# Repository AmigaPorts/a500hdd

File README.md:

# Amiga 500 ATA hard disk interface

Floppy-bootable HDD interface for Amiga 500. Achieves 600kB/s speed on
unexpanded system. Works well with kickstart 1.3 and 2.0.

Should you have two HDD expansions mounted for same address space, you can
invert master/slave select with a set of jumpers so that both can theoretically
coexist.

This board is bundled with side expansion adapter, which converts hard-to-get
edge connector into common pin header. For user convenience and safety of
PC mainboards with ISA slots, future expansions will be developed with pin
headers as their main connector.

**NOTE:** it is strongly recommended to wait for another revision of the board
since Rev2 has some minor, but annoying bugs.

## Release structure

Binary and gerber files are only packaged in releases.
For gerbers see `board/gerber` directory.
For device/software binaries see `software/bin` and `device/bin` directories.

## Documentation

If you feel that anything here needs elaborating, feel free to submit an issue.

- [Assembly](doc/assembly.md)
- [Preparing boot floppy](doc/floppy.md)
- [Formatting HDD for Amiga use](doc/formatting.md)

## License

Project's PCB designed is licensed under Creative Commons Attribution
Share-Alike (CC BY-SA) and is based on
[a500hdd](http://nuclear.mutantstargoat.com/hw/amiga/a500hdd)
by [John Tsiombikas](mailto:nuclear@member.fsf.org).

Code is licensed under Mozilla Public License version 2 (MPL2).
Original sources are taken from TODO project by TODO and TODO.

TL;DR: You have to publish your changes under same license, marking PCB design
with notice similar to one found in this project. For code changes, each file
with MPL header you modify must be published under same license.
Sharing is caring.

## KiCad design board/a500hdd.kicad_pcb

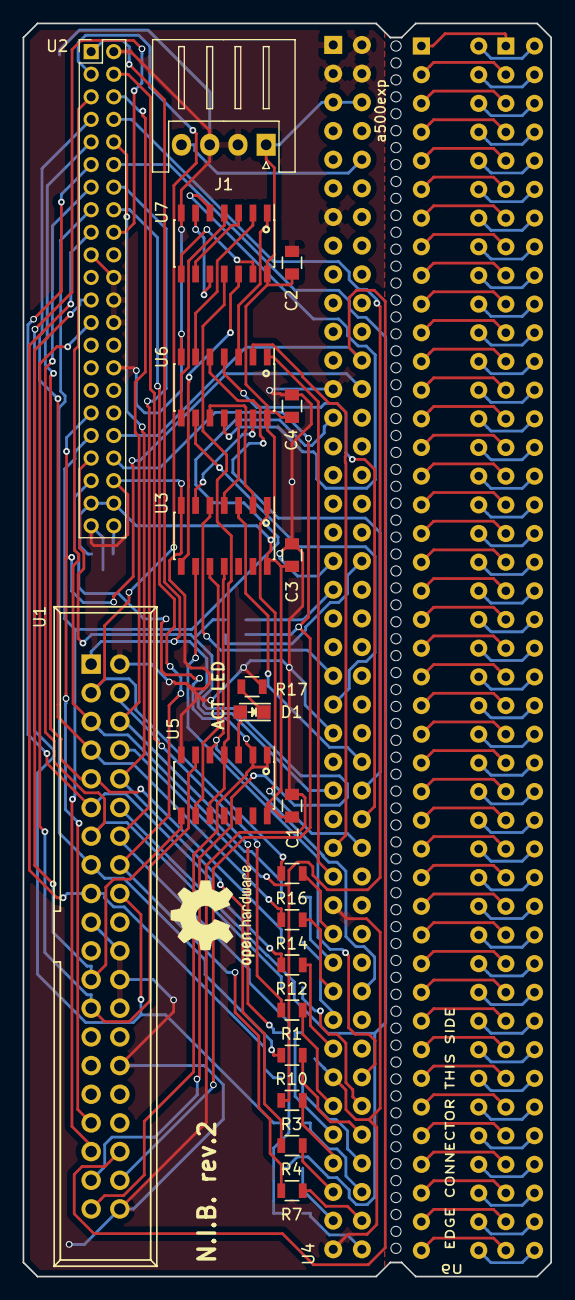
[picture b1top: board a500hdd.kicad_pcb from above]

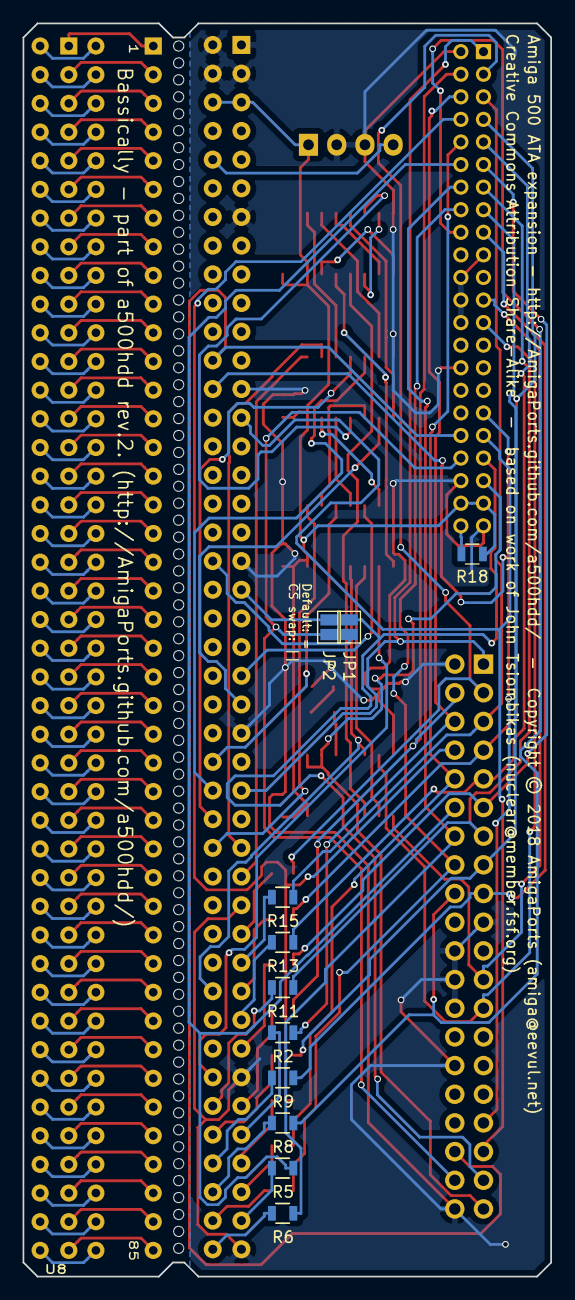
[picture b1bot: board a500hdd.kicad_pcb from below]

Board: 2 copper layers, 46.8 x 111.0 mm, 35 parts (11 on the bottom side), 158 nets.

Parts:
C1, C2, C3, C4: 0.1uF; C_0805
D1: LED; LED_0805
J1: Conn_01x04_Male; JST_XH_S04B-XH-A_1x04_P2.50mm_Horizontal
JP1, JP2: SolderJumper_2_Bridged; SolderJumper-2_P1.3mm_Open_Pad1.0x1.5mm
R1, R2, R3, R4, R5, R6, R7, R8, R9, R10, R11, R12, R13, R14, R15, R16: 68R; R_0805
R17: 330R; R_0805
R18: 4k7; R_0805
U1: ata_connector; IDC_Header_Straight_40pins
U2: ata_connector44; Pin_Header_Straight_2x22_Pitch2.00mm
U3: 74LS04; SOIC-14_3.9x8.7mm_Pitch1.27mm
U4, U8: a500exp; header2x43
U5: 74LS00; SOIC-14_3.9x8.7mm_Pitch1.27mm
U6, U7: 74LS08; SOIC-14_3.9x8.7mm_Pitch1.27mm
U9: a500exp; A500_Expansion_slot

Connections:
+12V: J1.4, U4.10
/D0: R1.1, U1.4, U2.4
/D1: R2.1, U1.6, U2.6
/D2: R3.1, U1.8, U2.8
/D3: R4.1, U1.10, U2.10
/D4: R5.1, U1.12, U2.12
/D5: R6.1, U1.14, U2.14
/D6: R7.1, U1.16, U2.16
/D7: R8.1, U1.18, U2.18
/D8: R9.1, U1.17, U2.17
/D9: R10.1, U1.15, U2.15
/D10: R11.1, U1.13, U2.13
/D11: R12.1, U1.11, U2.11
/D12: R13.1, U1.9, U2.9
/D13: R14.1, U1.7, U2.7
/D14: R15.1, U1.5, U2.5
/D15: R16.1, U1.3, U2.3
A16: U3.5, U4.45
A17: U4.47, U6.9
A18: U3.3, U4.52
A19: U4.54, U6.5
A20: U4.56, U6.4
A21: U3.1, U4.58
A22: U4.57, U6.2
A23: U4.59, U6.1
ATA_A0: U1.35, U2.35, U4.27
ATA_A1: U1.33, U2.33, U4.26
ATA_A2: U1.36, U2.36, U4.24
B7: U8.7, U9.7
B9: U8.9, U9.9
B11: U8.11, U9.11
B46: U8.46, U9.46
B48: U8.48, U9.48
B50: U8.50, U9.50
B51: U8.51, U9.51
B53: U8.53, U9.53
B55: U8.55, U9.55
B60: U8.60, U9.60
B61: U8.61, U9.61
B62: U8.62, U9.62
B63: U8.63, U9.63
B64: U8.64, U9.64
B65: U8.65, U9.65
B66: U8.66, U9.66
B67: U8.67, U9.67
B68: U8.68, U9.68
B69: U8.69, U9.69
B70: U8.70, U9.70
B71: U8.71, U9.71
B72: U8.72, U9.72
B73: U8.73, U9.73
B74: U8.74, U9.74
B75: U8.75, U9.75
B76: U8.76, U9.76
B77: U8.77, U9.77
B78: U8.78, U9.78
B79: U8.79, U9.79
B80: U8.80, U9.80
B81: U8.81, U9.81
B82: U8.82, U9.82
B83: U8.83, U9.83
B84: U8.84, U9.84
B85: U8.85, U9.85
B86: U8.86, U9.86
ENABLE: U5.4, U5.10, U7.11
GND: C1.2, C2.2, C3.2, C4.2, J1.2, J1.3, R17.1, U1.2, U1.19, U1.22, U1.24, U1.26, U1.30, U1.40, U2.2, U2.19, U2.22, U2.24, U2.26, U2.30, U2.40, U2.43, U3.7, U4.1, U4.2, U4.3, U4.4, U4.13, U4.25, U4.37, U4.49, U4.61, U4.73, U4.85, U5.7, U6.7, U7.7
unnamed: D1.1, R17.2
unnamed: D1.2, U5.3
unnamed: R1.2, U4.75
unnamed: R2.2, U4.77
unnamed: R3.2, U4.79
unnamed: R4.2, U4.81
unnamed: R5.2, U4.83
unnamed: R6.2, U4.86
unnamed: R7.2, U4.84
unnamed: R8.2, U4.82
unnamed: R9.2, U4.80
unnamed: R10.2, U4.78
unnamed: R11.2, U4.76
unnamed: R12.2, U4.71
unnamed: R13.2, U4.69
unnamed: R14.2, U4.67
unnamed: R15.2, U4.65
unnamed: R16.2, U4.63
unnamed: R18.1, U2.44
unnamed: U3.2, U6.10
unnamed: U3.4, U6.12
unnamed: U3.6, U6.13
unnamed: U3.8, U7.12
unnamed: U3.10, U5.9
unnamed: U6.3, U7.1
unnamed: U6.6, U7.2
unnamed: U6.8, U7.4
unnamed: U6.11, U7.5
unnamed: U7.3, U7.9
unnamed: U7.6, U7.10
unnamed: U7.8, U7.13
unnamed: U8.1, U9.1
unnamed: U8.2, U9.2
unnamed: U8.3, U9.3
unnamed: U8.4, U9.4
unnamed: U8.5, U9.5
unnamed: U8.6, U9.6
unnamed: U8.8, U9.8
unnamed: U8.10, U9.10
unnamed: U8.12, U9.12
unnamed: U8.13, U9.13
unnamed: U8.14, U9.14
unnamed: U8.15, U9.15
unnamed: U8.16, U9.16
unnamed: U8.17, U9.17
unnamed: U8.18, U9.18
unnamed: U8.19, U9.19
unnamed: U8.20, U9.20
unnamed: U8.21, U9.21
unnamed: U8.22, U9.22
unnamed: U8.23, U9.23
unnamed: U8.24, U9.24
unnamed: U8.25, U9.25
unnamed: U8.26, U9.26
unnamed: U8.27, U9.27
unnamed: U8.28, U9.28
unnamed: U8.29, U9.29
unnamed: U8.30, U9.30
unnamed: U8.31, U9.31
unnamed: U8.32, U9.32
unnamed: U8.33, U9.33
unnamed: U8.34, U9.34
unnamed: U8.35, U9.35
unnamed: U8.36, U9.36
unnamed: U8.37, U9.37
unnamed: U8.38, U9.38
unnamed: U8.39, U9.39
unnamed: U8.40, U9.40
unnamed: U8.41, U9.41
unnamed: U8.42, U9.42
unnamed: U8.43, U9.43
unnamed: U8.44, U9.44
unnamed: U8.45, U9.45
unnamed: U8.47, U9.47
unnamed: U8.49, U9.49
unnamed: U8.52, U9.52
unnamed: U8.54, U9.54
unnamed: U8.56, U9.56
unnamed: U8.57, U9.57
unnamed: U8.58, U9.58
unnamed: U8.59, U9.59
R/~W: U3.11, U4.68, U5.5
VCC: C1.1, C2.1, C3.1, C4.1, J1.1, R18.2, U2.41, U2.42, U3.14, U4.5, U4.6, U5.14, U6.14, U7.14
~AS: U3.9, U4.74
~ATA_ACTILED: U1.39, U2.39, U5.1, U5.2
~ATA_CS0: JP1.2, U1.37, U2.37
~ATA_CS1: JP2.2, U1.38, U2.38
~ATA_CSA: JP1.1, U4.38
~ATA_CSB: JP2.1, U4.39
~ATA_RD: U1.25, U2.25, U5.6
~ATA_RESET: U1.1, U2.1, U4.53
~ATA_WR: U1.23, U2.23, U5.8

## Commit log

2018-08-13 Imported sources to GitHub
2018-08-14 Added ATA44 header to schematic
2018-08-21 Rev2 PCB, migrated do KiCad5
2018-08-21 added beta notice
2018-09-01 reorganized files
2018-09-02 added LICENSE, initial documentation
2018-09-02 info about releases
2018-09-02 added note about using IDE44 female header
2018-09-02 added missing "Fitting LED" chapter
2018-09-02 added identify_drive sources
2018-09-02 added comment on address space, used stdint types
2018-09-02 photo
2018-09-08 fixed activity LED on schematic?
2018-09-08 One more capacitor is needed
2018-09-15 Single negation of LED signal by NAND should be enough
2018-11-10 fixed lib path
2018-11-11 added clockport connectors
2018-11-11 assignments done
2021-01-31 changed drills on board break line from PTH to NPTH

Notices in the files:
board/a500hdd.kicad_pcb:
Copyright (C) AmigaPorts
Creative Commons Attribution Share-Alike  -  based on work of John Tsiombikas (nuclear@member.fsf.org)
Amiga 500 ATA expansion - http://AmigaPorts.github.com/a500hdd/  -  Copyright © 2018 AmigaPorts (amiga@eevul.net)
